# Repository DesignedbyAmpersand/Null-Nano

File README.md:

The Null Nano is an ESP32 powered gaming handheld that uses retro-go from ducalex.

It measures 100x35x15mm and has roughly 3 hours of battery life.

This is not a beginner project.

These files are provided for free and with no guarantees.
These files are provided for personal use and not for resale purposes.

You will need the SD card skeleton files from here: https://1drv.ms/u/c/66cb300826c22fa3/Efv0uc86yZ5Hv4n83UHvBrcBqe-35vOahgP56gvEnUvf-g?e=ifL2Ww

You will also need the ESP32 flash download tool: https://1drv.ms/u/c/66cb300826c22fa3/EbNSYC88lTlOn8YUjpB1ucgBnk_qerDjQeKToj3xAFp3lw?e=woOXxG

Do not use a USB C to USB C cable to charge the Null Nano, it does not have anything connected to CC1 or CC2.

Do not use the Null Nano whilst charging, it does not have the necessary components to make this safe.

Use Kapton tape, do not use regular tape or masking tape.

You will need the latest version of the ESP flash tool to flash the Null Nano. Make sure you have installed the necessary drivers for your USB to UART adapter. The "options" button acts as a Boot button, so hold down options when you turn it on/provide power to enter bootloader mode for flashing.

The R3 resistor determines the charge rate. 1000/X = Y
e.g. for a 5.6K resistor the equation is 1000/5.6 = 179mA
If you use a different battery, you will need to change this resistor value.

The green LED goes on the right and the red LED on the left.

Trim the plastic pins off the bottom of the micro SD card socket with a scalpel or flush cutters (the holes needed would've interfered with the DPad).

The PCB needs to be 1.6mm thick. I order through JLCPCB and have "JLCJLCJLCJLC" written on the board so that the production number can be hidden below the ESP32.

The screws used are 8mm M2 self-tapping cap head

Resources used:

Odroid GO schematic
https://github.com/hardkernel/ODROID-GO/blob/master/Documents/ODROID-GO_REV0.1_20180518.pdf

Screen config file from this project
https://circuitdigest.com/microcontroller-projects/esp32-based-retro-game-console

Amp circuit based on Adafruit Class D amplifier
https://learn.adafruit.com/adafruit-pam8302-mono-2-5w-class-d-audio-amplifier

Charge circuit based on Adafruit MicroLiPo
https://learn.adafruit.com/adafruit-microlipo-and-minilipo-battery-chargers

Retro-go software
https://github.com/ducalex/retro-go

All graphics designed by me
The working title was "Wrigley" if you were wondering.

Let me know if you make one, have fun!
Ampersand

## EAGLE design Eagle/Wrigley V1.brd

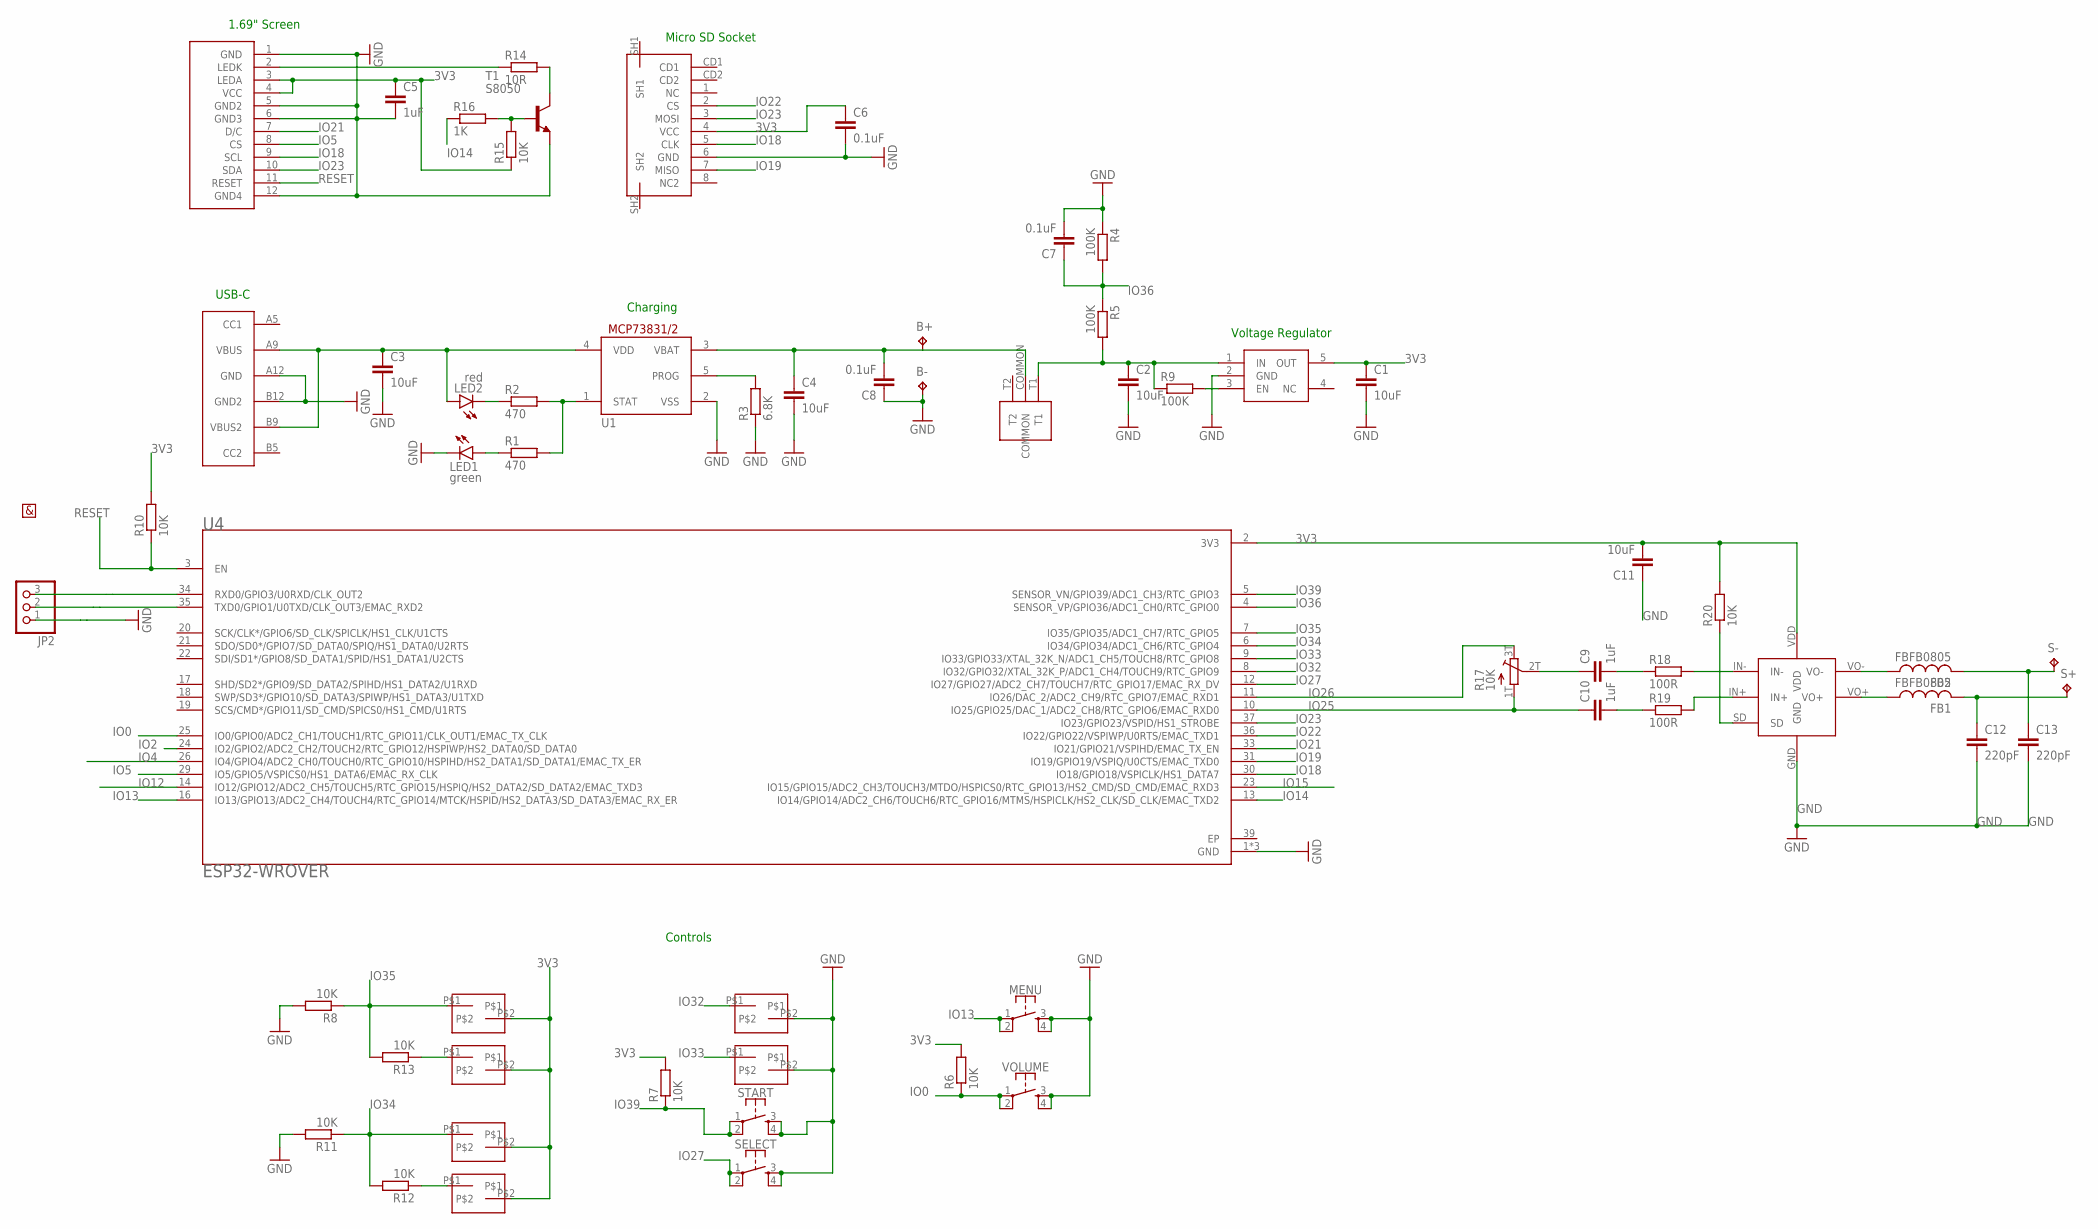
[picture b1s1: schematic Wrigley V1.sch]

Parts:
A: POCKET-BUTTONS-BIG; POCKET-MEMBRANE-BIG
B: POCKET-BUTTONS-BIG; POCKET-MEMBRANE-BIG
B+: TPTP20R; TP20R
B-: TPTP20R; TP20R
C1, C2, C3, C4, C11: 10uF; C0805
C5, C9, C10: 1uF; C0805
C6, C7, C8: 0.1uF; C0805
C12, C13: 220pF; C0805
DOWN: POCKET-BUTTONS-BIG; POCKET-MEMBRANE-BIG
FB1, FB2: FBFB0805; 0805
JP2: PINHD-1X03_2.54-S; 1X03-S
LED1: green; CHIP-LED0805
LED2: red; CHIP-LED0805
LEFT: POCKET-BUTTONS-BIG; POCKET-MEMBRANE-BIG
MENU: MOMENTARY-SWITCH-SPST-2-SMD-5.2MM; TACTILE_SWITCH_SMD_5.2MM
R1, R2: 470; R0805
R3: 6.8K; R0805
R4, R5, R9: 100K; M0805
R6, R7, R8, R10, R11, R12, R13, R15: 10K; M0805
R14: 10R; M0805
R16: 1K; M0805
R17: 10K; SLIDE-POT-RS08U11AZ001
R18, R19: 100R; R0805
R20: 10K; R0805
RIGHT: POCKET-BUTTONS-BIG; POCKET-MEMBRANE-BIG
S+: TPTP20R; TP20R
S-: TPTP20R; TP20R
SELECT: MOMENTARY-SWITCH-SPST-2-SMD-5.2MM; TACTILE_SWITCH_SMD_5.2MM
START: MOMENTARY-SWITCH-SPST-2-SMD-5.2MM; TACTILE_SWITCH_SMD_5.2MM
T1: S8050; SOT23-BEC
U1: MCP73831/OT; SOT23-5L
U2: AP2112-REGULATORWRIGLEY; SOT23-5L
U3: PAM8302A; PAM8302A-SOP8
U4: ESP32-WROVER; XCVR-ESP32-WROVER
U$1: MICROSD-SOCKET-RISTRETTONO-HOLES; MICROSD-SOCKET-WRIGLEY
U$3: 1.69-INCH-SCREEN-ROUNDED
U$5: NULL2-SWITCH
U$8: USB-C-6PIN
U$9: AMP-HALF
UP: POCKET-BUTTONS-BIG; POCKET-MEMBRANE-BIG
VOLUME: MOMENTARY-SWITCH-SPST-2-SMD-5.2MM; TACTILE_SWITCH_SMD_5.2MM

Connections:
3V3: C1.1, C5.1, C6.1, C11.2, DOWN.P$2, LEFT.P$2, R6.2, R7.2, R10.2, R15.1, R20.2, RIGHT.P$2, U2.5 (OUT), U3.VDD, U4.2 (3V3), U$1.4 (VCC), U$3.3 (LEDA), U$3.4 (VCC), UP.P$2
EP: U4.39 (EP)
GND: A.P$2, B.P$2, B-.TP, C1.2, C2.2, C3.2, C4.2, C5.2, C6.2, C7.2, C8.1, C11.1, C12.2, C13.2, JP2.1, LED1.C, MENU.3, MENU.4, R3.1, R4.1, R8.2, R11.2, SELECT.3, SELECT.4, START.3, START.4, T1.E, U1.2 (VSS), U2.2 (GND), U3.GND, U4.1 (GND), U4.15 (GND), U4.38 (GND), U$1.6 (GND), U$3.1 (GND), U$3.5 (GND2), U$3.6 (GND3), U$3.12 (GND4), U$8.A12 (GND), U$8.B12 (GND2), VOLUME.3, VOLUME.4
IO0: R6.1, U4.25 (IO0/GPIO0/ADC2_CH1/TOUCH1/RTC_GPIO11/CL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), VOLUME.1, VOLUME.2
IO2: U4.24 (IO2/GPIO2/ADC2_CH2/TOUCH2/RTC_GPIO12/HS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)
IO4: U4.26 (IO4/GPIO4/ADC2_CH0/TOUCH0/RTC_GPIO10/HS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)
IO5: U4.29 (IO5/GPIO5/VSPICS0/HS1_DATA6/EMAC_RX_CLK), U$3.8 (CS)
IO12: U4.14 (IO12/GPIO12/ADC2_CH5/TOUCH5/RTC_GPIO15/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)
IO13: MENU.1, MENU.2, U4.16 (IO13/GPIO13/ADC2_CH4/TOUCH4/RTC_GPIO14/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)
IO14: R16.1, U4.13 (IO14/GPIO14/ADC2_CH6/TOUCH6/RTC_GPIO16/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)
IO15: U4.23 (IO15/GPIO15/ADC2_CH3/TOUCH3/MTDO/HSPICS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)
IO18: U4.30 (IO18/GPIO18/VSPICLK/HS1_DATA7), U$1.5 (CLK), U$3.9 (SCL)
IO19: U4.31 (IO19/GPIO19/VSPIQ/U0CTS/EMAC_TXD0), U$1.7 (MISO)
IO21: U4.33 (IO21/GPIO21/VSPIHD/EMAC_TX_EN), U$3.7 (D/C)
IO22: U4.36 (IO22/GPIO22/VSPIWP/U0RTS/EMAC_TXD1), U$1.2 (CS)
IO23: U4.37 (IO23/GPIO23/VSPID/HS1_STROBE), U$1.3 (MOSI), U$3.10 (SDA)
IO25: C10.1, R17.1T (1), U4.10 (IO25/GPIO25/DAC_1/ADC2_CH8/RTC_GPIO6/EM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)
IO26: R17.3T (3), U4.11 (IO26/DAC_2/ADC2_CH9/RTC_GPIO7/EMAC_RXD1)
IO27: SELECT.1, SELECT.2, U4.12 (IO27/GPIO27/ADC2_CH7/TOUCH7/RTC_GPIO17/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)
IO32: A.P$1, U4.8 (IO32/GPIO32/XTAL_32K_P/ADC1_CH4/TOUCH9/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)
IO33: B.P$1, U4.9 (IO33/GPIO33/XTAL_32K_N/ADC1_CH5/TOUCH8/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)
IO34: LEFT.P$1, R11.1, R12.2, U4.6 (IO34/GPIO34/ADC1_CH6/RTC_GPIO4)
IO35: R8.1, R13.2, U4.7 (IO35/GPIO35/ADC1_CH7/RTC_GPIO5), UP.P$1
IO36: C7.1, R4.2, R5.1, U4.4 (SENSOR_VP/GPIO36/ADC1_CH0/RTC_GPIO0)
IO39: R7.1, START.1, START.2, U4.5 (SENSOR_VN/GPIO39/ADC1_CH3/RTC_GPIO3)
unnamed: R9.2, U2.3 (EN)
unnamed: C2.1, R5.2, R9.1, U2.1 (IN), U$5.T1
unnamed: R3.2, U1.5 (PROG)
unnamed: R1.2, R2.2, U1.1 (STAT)
unnamed: LED2.C, R2.1
unnamed: LED1.A, R1.1
unnamed: DOWN.P$1, R13.1
unnamed: C3.1, LED2.A, U1.4 (VDD), U$8.A9 (VBUS), U$8.B9 (VBUS2)
unnamed: B+.TP, C4.1, C8.2, U1.3 (VBAT), U$5.COMMON
unnamed: R14.1, U$3.2 (LEDK)
unnamed: JP2.3, U4.34 (RXD0/GPIO3/U0RXD/CLK_OUT2)
unnamed: JP2.2, U4.35 (TXD0/GPIO1/U0TXD/CLK_OUT3/EMAC_RXD2)
unnamed: R14.2, T1.C
unnamed: R15.2, R16.2, T1.B
unnamed: R12.1, RIGHT.P$1
unnamed: C9.1, R17.2T (2)
unnamed: C9.2, R18.1
unnamed: C10.2, R19.1
unnamed: R18.2, U3.IN-
unnamed: R19.2, U3.IN+
unnamed: C13.1, FB2.2, S-.TP
unnamed: C12.1, FB1.2, S+.TP
unnamed: FB2.1, U3.VO-
unnamed: FB1.1, U3.VO+
unnamed: R20.1, U3.SD
RESET: R10.1, U4.3 (EN), U$3.11 (RESET)

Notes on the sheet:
USB-C
Charging
Voltage Regulator
Controls
Micro SD Socket
1.69" Screen

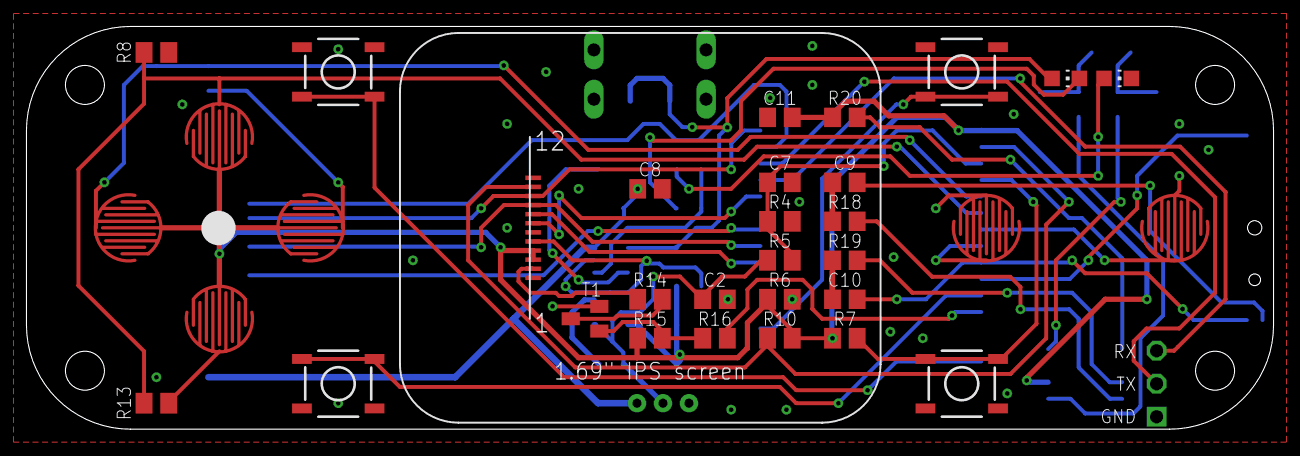
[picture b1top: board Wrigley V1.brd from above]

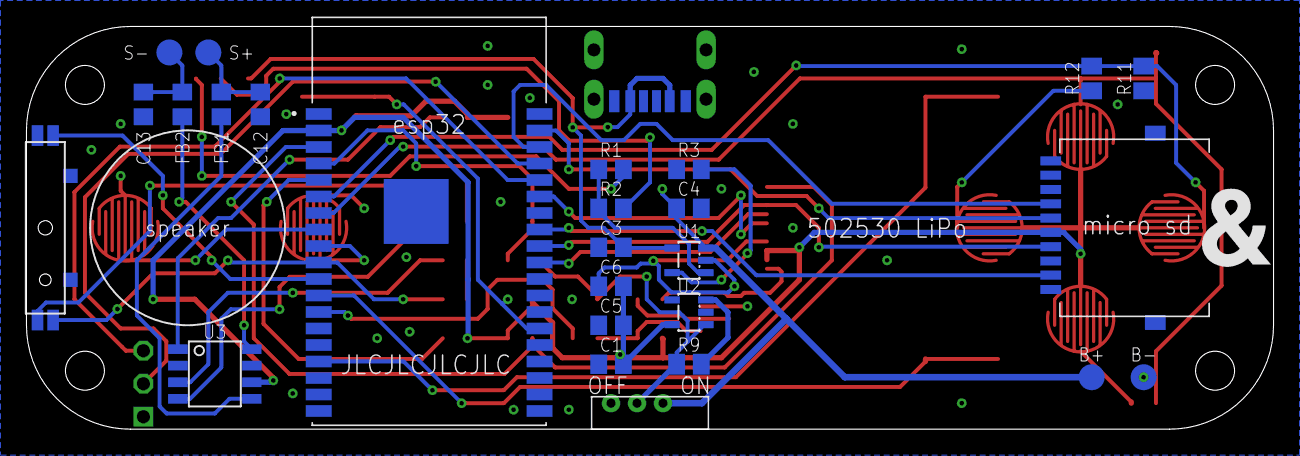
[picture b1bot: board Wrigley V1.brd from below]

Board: 2 copper layers, 96.0 x 31.0 mm, 62 parts (28 on the bottom side), 46 nets.

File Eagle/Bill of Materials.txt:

Part   Value                            Device                            Package                  Description
C1     10uF                             C-EUC0805                         C0805                    CAPACITOR
C2     10uF                             C-EUC0805                         C0805                    CAPACITOR
C3     10uF                             C-EUC0805                         C0805                    CAPACITOR
C4     10uF                             C-EUC0805                         C0805                    CAPACITOR
C5     1uF                              C-EUC0805                         C0805                    CAPACITOR
C6     0.1uF                            C-EUC0805                         C0805                    CAPACITOR
C7     0.1uF                            C-EUC0805                         C0805                    CAPACITOR
C8     0.1uF                            C-EUC0805                         C0805                    CAPACITOR
C9     1uF                              C-EUC0805                         C0805                    CAPACITOR
C10    1uF                              C-EUC0805                         C0805                    CAPACITOR
C11    10uF                             C-EUC0805                         C0805                    CAPACITOR
C12    220pF                            C-EUC0805                         C0805                    CAPACITOR
C13    220pF                            C-EUC0805                         C0805                    CAPACITOR
FB1    FBFB0805                         FBFB0805                          0805                     Ferrite bead                                                                                                  
FB2    FBFB0805                         FBFB0805                          0805                     Ferrite bead                                                                                                  
LED1   green                            LEDCHIP-LED0805                   CHIP-LED0805             The LED on the left
LED2   red                              LEDCHIP-LED0805                   CHIP-LED0805             The LED on the right
R1     470                              R-EU_R0805                        R0805                    RESISTOR, European symbol                                                                                     
R2     470                              R-EU_R0805                        R0805                    RESISTOR, European symbol                                                                                     
R3     5.6K                             R-EU_R0805                        R0805                    RESISTOR, European symbol                                                                                     
R4     100K                             R-EU_M0805                        M0805                    RESISTOR, European symbol                                                                                     
R5     100K                             R-EU_M0805                        M0805                    RESISTOR, European symbol                                                                                     
R6     10K                              R-EU_M0805                        M0805                    RESISTOR, European symbol                                                                                     
R7     10K                              R-EU_M0805                        M0805                    RESISTOR, European symbol                                                                                     
R8     10K                              R-EU_M0805                        M0805                    RESISTOR, European symbol                                                                                     
R9     100K                             R-EU_M0805                        M0805                    RESISTOR, European symbol                                                                                     
R10    10K                              R-EU_M0805                        M0805                    RESISTOR, European symbol                                                                                     
R11    10K                              R-EU_M0805                        M0805                    RESISTOR, European symbol                                                                                     
R12    10K                              R-EU_M0805                        M0805                    RESISTOR, European symbol                                                                                     
R13    10K                              R-EU_M0805                        M0805                    RESISTOR, European symbol                                                                                     
R14    10R                              R-EU_M0805                        M0805                    RESISTOR, European symbol                                                                                     
R15    10K                              R-EU_M0805                        M0805                    RESISTOR, European symbol                                                                                     
R16    1K                               R-EU_M0805                        M0805                    RESISTOR, European symbol                                                                                     
R18    100R                             R-EU_R0805                        R0805                    RESISTOR, European symbol
R19    100R                             R-EU_R0805                        R0805                    RESISTOR, European symbol
R20    10K                              R-EU_R0805                        R0805                    RESISTOR, European symbol
T1     S8050                            S8050                             SOT23-BEC                                                                                                                              
U1     MCP73831/OT                      MCP73831/OT                       SOT23-5L                 MCP73831/2                                                                                                    
U2     AP2112-REGULATOR                 AP2112-REGULATOR                  SOT23-5L                                                                                                                               
U3     PAM8302A                         PAM8302A                          SOP8
